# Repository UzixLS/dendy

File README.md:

## Dendy
Yet another Dendy (Famicom) clone - 8-bit home video game console

[(more random photos there)](https://cloud.err200.net/index.php/s/73TR85tYZkMm8Ax?path=%2Fdendy)

- PCB optimized for NewGame's case
- Almost all components is DIP (THT)
- 9-12V DC power supply with any polarity
- Step-down switching regulator
- PNP+NPN transistors-based video amplifier
- OpAmp-based audio mixer/amplifier
- Two switchable quartz crystals (PAL+NTSC)

### Changelog & current status
* Rev.A - first release. Please note the [errata](pcb/rev.A/ERRATA.txt)
* Rev.B:
    - Reworked crystal generator circuit
    - Tuned pcb's dimensions and holes placement for better compatibility with enclosures
    - Various minor changes and improvements
* Rev.B1:
    - Power switch moved up to 0.5mm
    - Various minor changes and improvements

### Credits
I want to express my appreciation to the
 - megawalkman
 - HardWareMan
 - lm2000
 - HotPixel

authors of the following projects, which served as inspiration and as reference for my development:

- https://www.emu-land.net/forum/index.php/topic,75737.0.html - Dendy Classic/Junior Steepler Remake
- https://www.emu-land.net/forum/index.php/topic,78815.0.html - Dendy Junior Remastered
- https://github.com/mleonid2000/dendy_junior_remastered - Dendy Junior Remastered
- https://github.com/HotPixelChannel/Candy_8bit - Candy 8bit system

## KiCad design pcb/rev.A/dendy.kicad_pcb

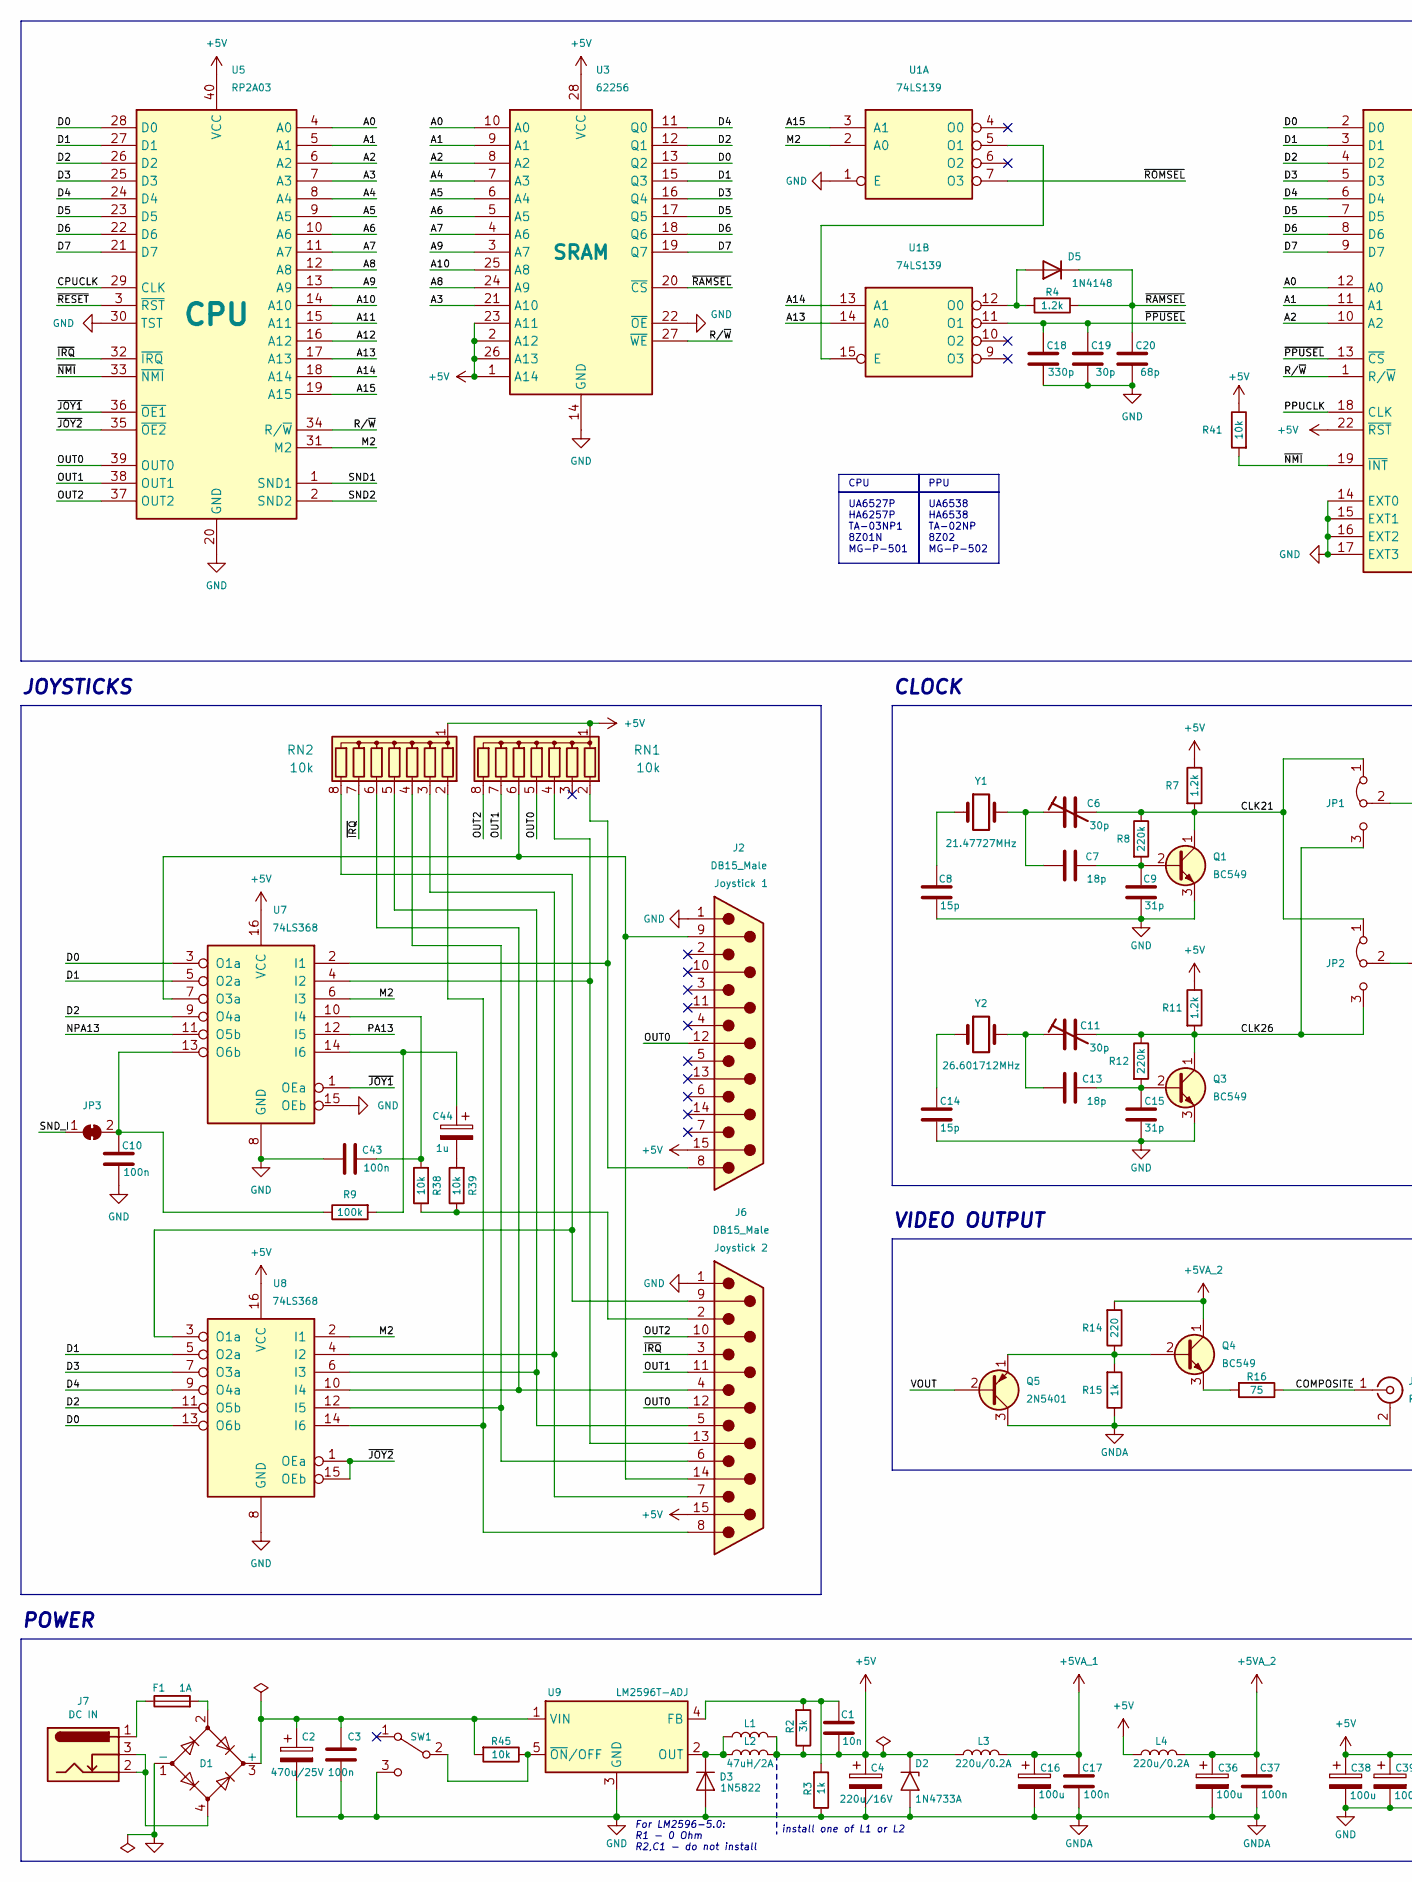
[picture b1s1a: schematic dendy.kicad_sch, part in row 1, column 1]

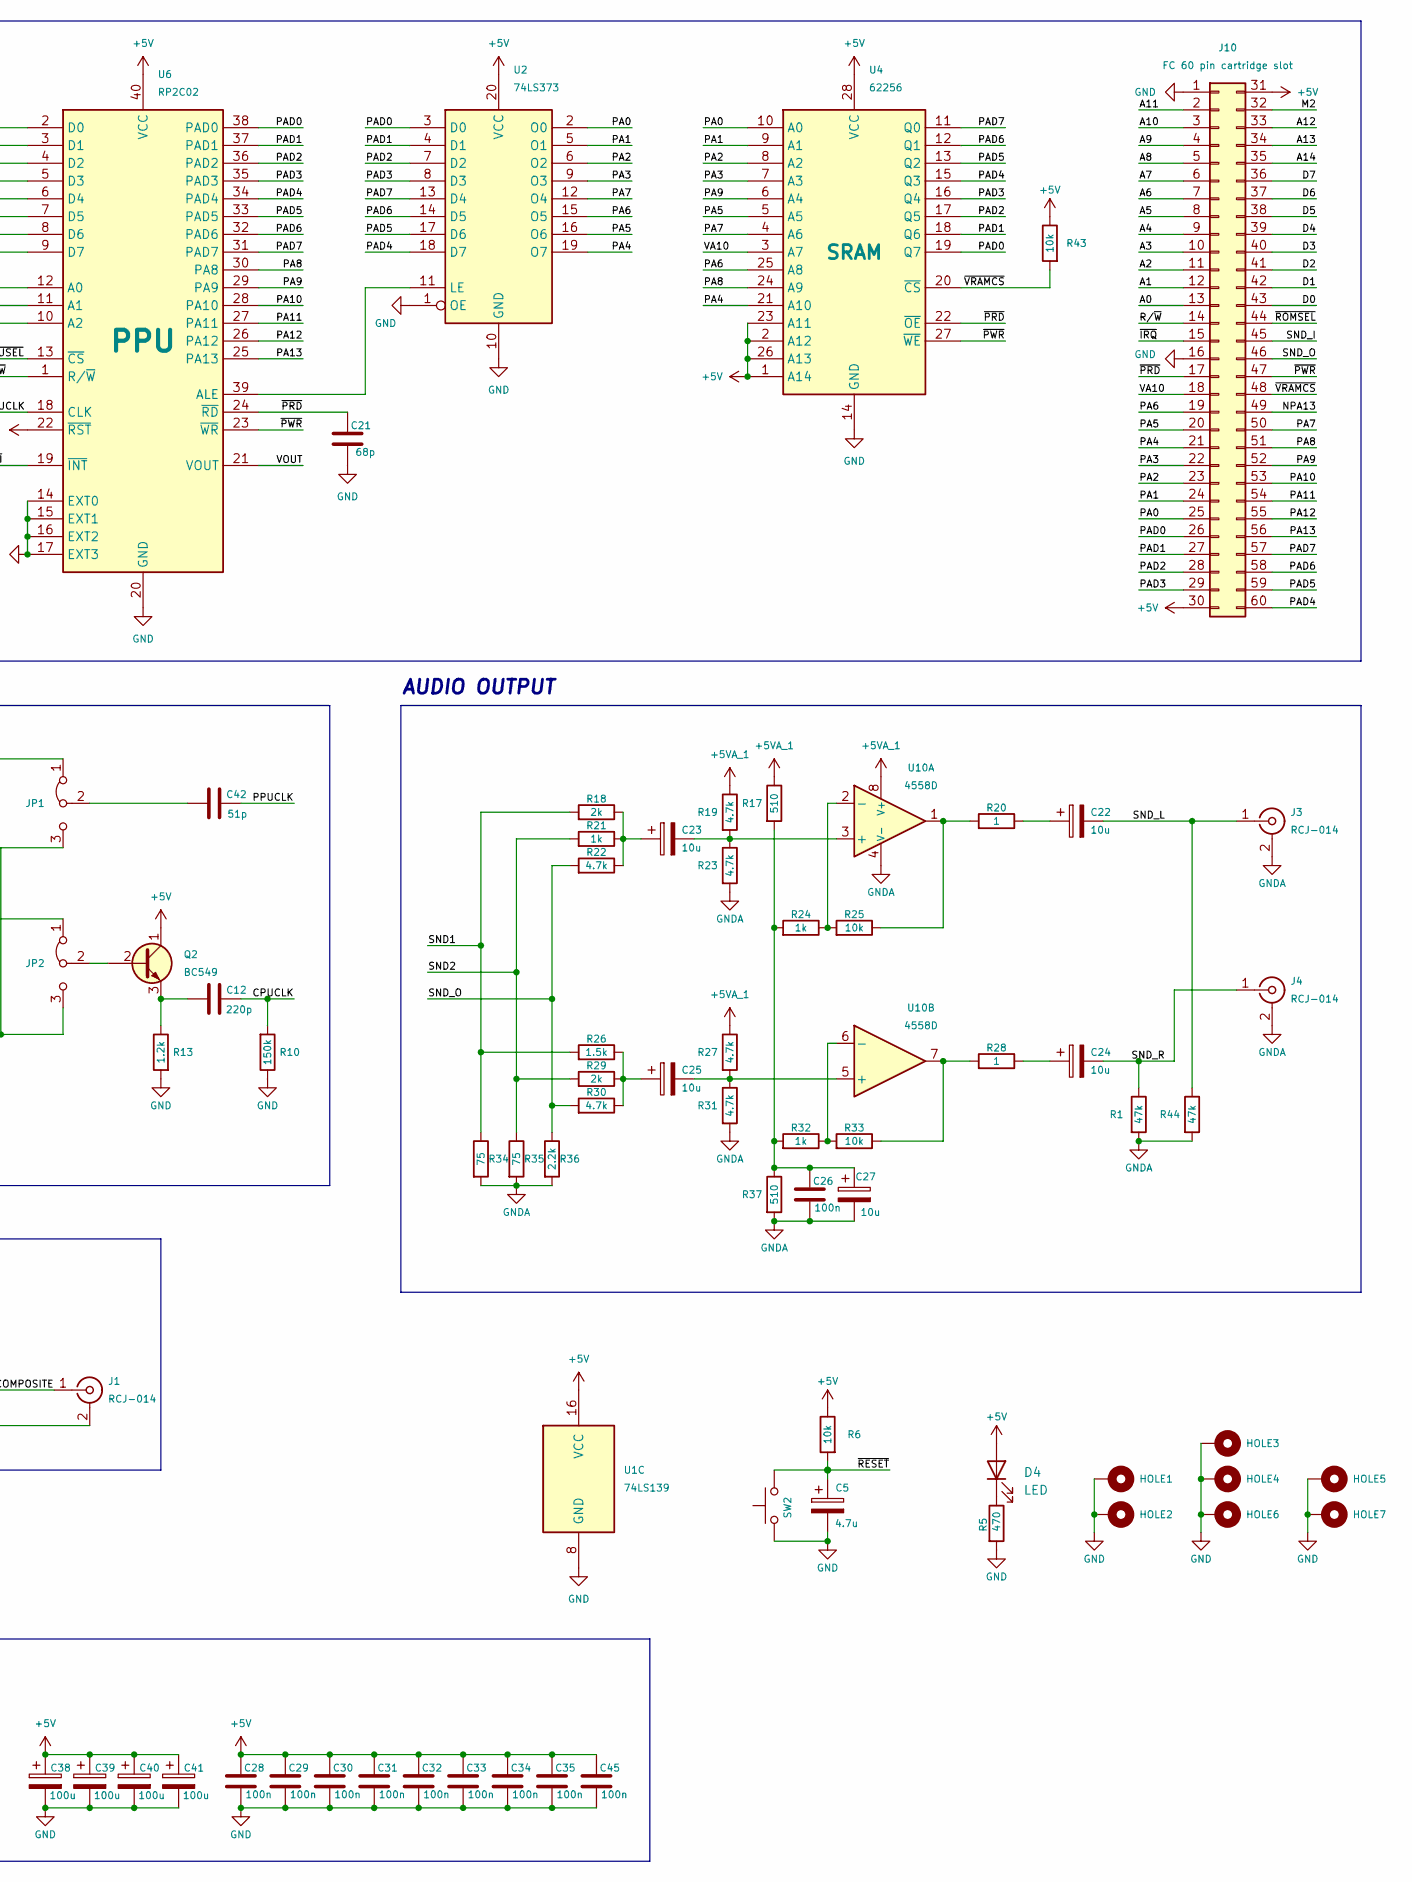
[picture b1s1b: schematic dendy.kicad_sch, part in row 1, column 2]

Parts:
C1: 10n; C_Disc_D5.0mm_W2.5mm_P2.50mm
C2: 470u/25V; CP_Radial_D10.0mm_P5.00mm
C3, C10, C17, C26, C28, C29, C30, C31, C32, C33, C34, C35, C37, C43, C45: 100n; C_Disc_D5.0mm_W2.5mm_P2.50mm
C4: 220u/16V; CP_Radial_D8.0mm_P3.50mm
C5: 4.7u; CP_Radial_D4.0mm_P2.00mm
C6, C11: 30p; C_Trimmer_GKU_L5.6mm_W5.0mm_P5.8mm
C7, C13: 18p; C_Disc_D5.0mm_W2.5mm_P2.50mm
C8, C14: 15p; C_Disc_D5.0mm_W2.5mm_P2.50mm
C9, C15: 31p; C_Disc_D5.0mm_W2.5mm_P2.50mm
C12: 220p; C_Disc_D5.0mm_W2.5mm_P2.50mm
C16, C36, C38, C39, C40, C41: 100u; CP_Radial_D6.3mm_P2.50mm
C18: 330p; C_Disc_D5.0mm_W2.5mm_P2.50mm
C19: 30p; C_Disc_D5.0mm_W2.5mm_P2.50mm
C20, C21: 68p; C_Disc_D5.0mm_W2.5mm_P2.50mm
C22, C23, C24, C25, C27: 10u; CP_Radial_D4.0mm_P2.00mm
C42: 51p; C_Disc_D5.0mm_W2.5mm_P2.50mm
C44: 1u; CP_Radial_D4.0mm_P2.00mm
D1: 2W10; Diode_Bridge_Round_D10.0mm
D2: 1N4733A; D_DO-41_SOD81_P10.16mm_Horizontal
D3: 1N5822; D_DO-201AD_P15.24mm_Horizontal
D4: LED; LED_D5.0mm
D5: 1N4148; D_DO-35_SOD27_P7.62mm_Horizontal
F1: 1A; Fuse_1812_4532Metric_Pad1.30x3.40mm_HandSolder
HOLE1: HOLE; MountingHole_3.2mm_M3_Pad_Via
HOLE2: HOLE; MountingHole_4mm_Pad_Via
HOLE3, HOLE4, HOLE5, HOLE6, HOLE7: HOLE; MountingHole_3.2mm_M3_DIN965_Pad
J1, J3, J4: RCJ-014; CUI_RCJ-01X
J2, J6: DB15_Male; DSUB-15_Male_Horizontal_P2.77x2.54mm_EdgePinOffset9.40mm
J7: DS-210; BarrelJack_Horizontal
J10: FC 60 pin cartridge slot; FC60
JP1, JP2: Jumper_3_Bridged12; PinHeader_1x03_P2.54mm_Vertical
JP3: SolderJumper_2_Bridged; SolderJumper-2_P1.3mm_Bridged_RoundedPad1.0x1.5mm
L1: 47uH/2A; L_12x12mm_H8mm
L2: 47uH/2A; L_Radial_D8.7mm_P5.00mm_Fastron_07HCP
L3, L4: 220u/0.2A; L_Radial_D8.7mm_P5.00mm_Fastron_07HCP
Q1, Q2, Q3, Q4: BC549; TO-92_Inline_Wide_CBE
Q5: 2N5401; TO-92_Inline_Wide_EBC
R1, R44: 47k; R_Axial_DIN0207_L6.3mm_D2.5mm_P7.62mm_Horizontal
R2: 3k; R_Axial_DIN0207_L6.3mm_D2.5mm_P7.62mm_Horizontal
R3, R15, R21, R24, R32: 1k; R_Axial_DIN0207_L6.3mm_D2.5mm_P7.62mm_Horizontal
R4, R7, R11, R13: 1.2k; R_Axial_DIN0207_L6.3mm_D2.5mm_P7.62mm_Horizontal
R5: 470; R_Axial_DIN0207_L6.3mm_D2.5mm_P7.62mm_Horizontal
R6, R25, R33, R38, R39, R41, R43, R45: 10k; R_Axial_DIN0207_L6.3mm_D2.5mm_P7.62mm_Horizontal
R8, R12: 220k; R_Axial_DIN0207_L6.3mm_D2.5mm_P7.62mm_Horizontal
R9: 100k; R_Axial_DIN0207_L6.3mm_D2.5mm_P7.62mm_Horizontal
R10: 150k; R_Axial_DIN0207_L6.3mm_D2.5mm_P7.62mm_Horizontal
R14: 220; R_Axial_DIN0207_L6.3mm_D2.5mm_P7.62mm_Horizontal
R16, R34, R35: 75; R_Axial_DIN0207_L6.3mm_D2.5mm_P7.62mm_Horizontal
R17, R37: 510; R_Axial_DIN0207_L6.3mm_D2.5mm_P7.62mm_Horizontal
R18, R29: 2k; R_Axial_DIN0207_L6.3mm_D2.5mm_P7.62mm_Horizontal
R19, R22, R23, R27, R30, R31: 4.7k; R_Axial_DIN0207_L6.3mm_D2.5mm_P7.62mm_Horizontal
R20, R28: 1; R_Axial_DIN0207_L6.3mm_D2.5mm_P7.62mm_Horizontal
R26: 1.5k; R_Axial_DIN0207_L6.3mm_D2.5mm_P7.62mm_Horizontal
R36: 2.2k; R_Axial_DIN0207_L6.3mm_D2.5mm_P7.62mm_Horizontal
RN1, RN2: 10k; R_Array_SIP8
SW1: SW_SPDT; SS12F44G5
SW2: Button THT; FC_Reset_Switch_Universal
U1: 74LS139; DIP-16_W7.62mm
U2: 74LS373; DIP-20_W7.62mm
U3, U4: 62256; DIP-28_W7.62mm
U5: RP2A03; DIP-40_W15.24mm_Socket
U6: RP2C02; DIP-40_W15.24mm_Socket
U7, U8: 74LS368; DIP-16_W7.62mm
U9: LM2596T-ADJ; TO-220-263-5_Horizontal_TabDown
U10: 4558D; DIP-8_W7.62mm_LongPads
Y1: 21.47727MHz; Crystal_HC49-U_Vertical
Y2: 26.601712MHz; Crystal_HC49-U_Vertical

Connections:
+5V: C1.1, C4.1, C28.2, C29.2, C30.2, C31.2, C32.2, C33.2, C34.2, C35.2, C38.1, C39.1, C40.1, C41.1, C45.2, D2.1 (A1), D4.2 (A), J2.15, J6.15, J10.30, J10.31, L1.2, L2.2, L3.1, L4.1, Q2.1 (C), R2.1, R6.1, R7.1, R11.1, R41.1, R43.1, RN1.1 (common), RN2.1 (common), U1.16 (VCC), U2.20 (VCC), U3.1 (A14), U3.2 (A12), U3.23 (A11), U3.26 (A13), U3.28 (VCC), U4.1 (A14), U4.2 (A12), U4.23 (A11), U4.26 (A13), U4.28 (VCC), U5.40 (VCC), U6.22 (~RST), U6.40 (VCC), U7.16 (VCC), U8.16 (VCC)
+5VA_1: C16.1, C17.2, L3.2, R17.1, R19.1, R27.1, U10.8 (V+)
+5VA_2: C36.1, C37.2, L4.2, Q4.1 (C), R14.2
/A0: J10.13, U3.10 (A0), U5.4 (A0), U6.12 (A0)
/A1: J10.12, U3.9 (A1), U5.5 (A1), U6.11 (A1)
/A2: J10.11, U3.8 (A2), U5.6 (A2), U6.10 (A2)
/A3: J10.10, U3.21 (A10), U5.7 (A3)
/A4: J10.9, U3.7 (A3), U5.8 (A4)
/A5: J10.8, U3.6 (A4), U5.9 (A5)
/A6: J10.7, U3.5 (A5), U5.10 (A6)
/A7: J10.6, U3.4 (A6), U5.11 (A7)
/A8: J10.5, U3.24 (A9), U5.12 (A8)
/A9: J10.4, U3.3 (A7), U5.13 (A9)
/A10: J10.3, U3.25 (A8), U5.14 (A10)
/A11: J10.2, U5.15 (A11)
/A12: J10.33, U5.16 (A12)
/A13: J10.34, U1.14 (A0), U5.17 (A13)
/A14: J10.35, U1.13 (A1), U5.18 (A14)
/A15: U1.3 (A1), U5.19 (A15)
/CLK21: C6.2, JP1.1 (A), JP2.1 (A), Q1.1 (C), R7.2, R8.1
/CLK26: C11.2, JP1.3 (B), JP2.3 (B), Q3.1 (C), R11.2, R12.1
/COMPOSITE: J1.1 (In), R16.1
/CPUCLK: C12.2, R10.2, U5.29 (CLK)
/D0: J10.43, U3.13 (Q2), U5.28 (D0), U6.2 (D0), U7.3 (O1a), U8.13 (O6b)
/D1: J10.42, U3.15 (Q3), U5.27 (D1), U6.3 (D1), U7.5 (O2a), U8.5 (O2a)
/D2: J10.41, U3.12 (Q1), U5.26 (D2), U6.4 (D2), U7.9 (O4a), U8.11 (O5b)
/D3: J10.40, U3.16 (Q4), U5.25 (D3), U6.5 (D3), U8.7 (O3a)
/D4: J10.39, U3.11 (Q0), U5.24 (D4), U6.6 (D4), U8.9 (O4a)
/D5: J10.38, U3.17 (Q5), U5.23 (D5), U6.7 (D5)
/D6: J10.37, U3.18 (Q6), U5.22 (D6), U6.8 (D6)
/D7: J10.36, U3.19 (Q7), U5.21 (D7), U6.9 (D7)
/M2: J10.32, U1.2 (A0), U5.31 (M2), U7.6 (I3), U8.2 (I1)
/NPA13: J10.49, U7.11 (O5b)
/OUT0: J2.12, J6.12, RN1.5 (R4), U5.39 (OUT0)
/OUT1: J6.11 (P111), RN1.7 (R6), U5.38 (OUT1)
/OUT2: J6.10, RN1.8 (R7), U5.37 (OUT2)
/PA0: J10.25, U2.2 (O0), U4.10 (A0)
/PA1: J10.24, U2.5 (O1), U4.9 (A1)
/PA2: J10.23, U2.6 (O2), U4.8 (A2)
/PA3: J10.22, U2.9 (O3), U4.7 (A3)
/PA4: J10.21, U2.19 (O7), U4.21 (A10)
/PA5: J10.20, U2.16 (O6), U4.5 (A5)
/PA6: J10.19, U2.15 (O5), U4.25 (A8)
/PA7: J10.50, U2.12 (O4), U4.4 (A6)
/PA8: J10.51, U4.24 (A9), U6.30 (PA8)
/PA9: J10.52, U4.6 (A4), U6.29 (PA9)
/PA10: J10.53, U6.28 (PA10)
/PA11: J10.54, U6.27 (PA11)
/PA12: J10.55, U6.26 (PA12)
/PA13: J10.56, U6.25 (PA13), U7.12 (I5)
/PAD0: J10.26, U2.3 (D0), U4.19 (Q7), U6.38 (PAD0)
/PAD1: J10.27, U2.4 (D1), U4.18 (Q6), U6.37 (PAD1)
/PAD2: J10.28, U2.7 (D2), U4.17 (Q5), U6.36 (PAD2)
/PAD3: J10.29, U2.8 (D3), U4.16 (Q4), U6.35 (PAD3)
/PAD4: J10.60, U2.18 (D7), U4.15 (Q3), U6.34 (PAD4)
/PAD5: J10.59, U2.17 (D6), U4.13 (Q2), U6.33 (PAD5)
/PAD6: J10.58, U2.14 (D5), U4.12 (Q1), U6.32 (PAD6)
/PAD7: J10.57, U2.13 (D4), U4.11 (Q0), U6.31 (PAD7)
/PPUCLK: C42.2, U6.18 (CLK)
/R/~W: J10.14, U3.27 (~WE), U5.34 (R/~W), U6.1 (R/~W)
/SND1: R18.2, R26.2, R34.1, U5.1 (SND1)
/SND2: R21.2, R29.2, R35.1, U5.2 (SND2)
/SND_I: J10.45, JP3.1 (A)
/SND_L: C22.2, J3.1 (In), R44.1
/SND_O: J10.46, R22.2, R30.2, R36.1
/SND_R: C24.2, J4.1 (In), R1.1
/VA10: J10.18, U4.3 (A7)
/VOUT: Q5.2 (B), U6.21 (VOUT)
/~IRQ: J6.3, J10.15, RN2.7 (R6), U5.32 (~IRQ)
/~JOY1: U5.36 (~OE1), U7.1 (OEa)
/~JOY2: U5.35 (~OE2), U8.1 (OEa), U8.15 (OEb)
/~NMI: R41.2, U5.33 (~NMI), U6.19 (~INT)
/~PPUSEL: C18.2, C19.2, U1.11 (O1), U6.13 (~CS)
/~PRD: C21.2, J10.17, U4.22 (~OE), U6.24 (~RD)
/~PWR: J10.47, U4.27 (~WE), U6.23 (~WR)
/~RAMSEL: C20.2, D5.1 (K), R4.1, U3.20 (~CS)
/~RESET: C5.1, R6.2, SW2.2, U5.3 (~RST)
/~ROMSEL: J10.44, U1.7 (O3)
/~VRAMCS: J10.48, R43.2, U4.20 (~CS)
GND: C2.2, C3.2, C4.2, C5.2, C8.1, C9.1, C10.1, C14.1, C15.1, C16.2, C17.1, C18.1, C19.1, C20.1, C21.1, C26.1, C27.2, C28.1, C29.1, C30.1, C31.1, C32.1, C33.1, C34.1, C35.1, C36.2, C37.1, C38.2, C39.2, C40.2, C41.2, C43.1, C45.1, D1.1 (-), D2.2 (A2), D3.2 (A), HOLE1.1, HOLE2.1, HOLE3.1, HOLE4.1, HOLE5.1, HOLE6.1, HOLE7.1, J1.2 (Ext), J2.1, J3.2 (Ext), J4.2 (Ext), J6.1, J10.1, J10.16, Q1.3 (E), Q3.3 (E), Q5.3 (C), R1.2, R3.1, R5.2, R10.1, R13.2, R15.1, R23.2, R31.2, R34.2, R35.2, R36.2, R37.2, R44.2, SW1.3 (C), SW2.1, U1.1 (E), U1.8 (GND), U2.1 (OE), U2.10 (GND), U3.14 (GND), U3.22 (~OE), U4.14 (GND), U5.20 (GND), U5.30 (TST), U6.14 (EXT0), U6.15 (EXT1), U6.16 (EXT2), U6.17 (EXT3), U6.20 (GND), U7.8 (GND), U7.15 (OEb), U8.8 (GND), U9.3 (GND), U10.4 (V-)
unnamed: C6.1, C7.1, Y1.2
unnamed: C8.2, Y1.1
unnamed: C11.1, C13.1, Y2.2
unnamed: C14.2, Y2.1
unnamed: C22.1, R20.1
unnamed: C23.1, R18.1, R21.1, R22.1
unnamed: C24.1, R28.1
unnamed: C25.1, R26.1, R29.1, R30.1
unnamed: C26.2, C27.1, R17.2, R24.2, R32.2, R37.1
unnamed: C44.2, R39.2
unnamed: C2.1, C3.1, D1.3 (+), R45.2, U9.1 (VIN)
unnamed: D1.2, F1.2
unnamed: D1.4, J7.2, J7.3
unnamed: D3.1 (K), L1.1, L2.1, U9.2 (OUT)
unnamed: D4.1 (K), R5.1
unnamed: D5.2 (A), R4.2, U1.12 (O0)
unnamed: F1.1, J7.1
unnamed: J2.9, J6.14, RN1.6 (R5), U7.7 (O3a)
unnamed: J6.9, RN2.8 (R7), U8.3 (O1a)
unnamed: J6.13, RN1.4 (R3), U7.4 (I2)
unnamed: J6.2, R38.1, R39.1
unnamed: C42.1, JP1.2 (C)
unnamed: JP2.2 (C), Q2.2 (B)
unnamed: C10.2, JP3.2 (B), R9.1, U7.13 (O6b)
unnamed: C7.2, C9.2, Q1.2 (B), R8.2
unnamed: C12.1, Q2.3 (E), R13.1
unnamed: C13.2, C15.2, Q3.2 (B), R12.2
unnamed: Q4.2 (B), Q5.1 (E), R14.1, R15.2
unnamed: Q4.3 (E), R16.2
unnamed: R20.2, R25.1, U10.1
unnamed: R28.2, R33.1, U10.7
unnamed: J2.8, RN1.2 (R1), U7.2 (I1)
unnamed: J6.8, RN2.2 (R1), U8.14 (I6)
unnamed: J6.7, RN2.3 (R2), U8.4 (I2)
unnamed: J6.6, RN2.4 (R3), U8.12 (I5)
unnamed: J6.5, RN2.5 (R4), U8.6 (I3)
unnamed: J6.4, RN2.6 (R5), U8.10 (I4)
unnamed: R45.1, SW1.2 (B), U9.5 (~ON/OFF)
unnamed: U1.5 (O1), U1.15 (E)
unnamed: U2.11 (LE), U6.39 (ALE)
unnamed: C43.2, R38.2, U7.10 (I4)
unnamed: C44.1, R9.2, U7.14 (I6)
unnamed: C1.2, R2.2, R3.2, U9.4 (FB)
unnamed: C23.2, R19.2, R23.1, U10.3 (+)
unnamed: R24.1, R25.2, U10.2 (-)
unnamed: C25.2, R27.2, R31.1, U10.5 (+)
unnamed: R32.1, R33.2, U10.6 (-)

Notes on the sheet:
CPU
CLOCK
install one of L1 or L2
PPU
UA6527P HA6257P TA-03NP1 8Z01N MG-P-501
UA6538 HA6538 TA-02NP 8Z02 MG-P-502
VIDEO OUTPUT
POWER
For LM2596-5.0: R1 - 0 Ohm R2,C1 - do not install
AUDIO OUTPUT
JOYSTICKS

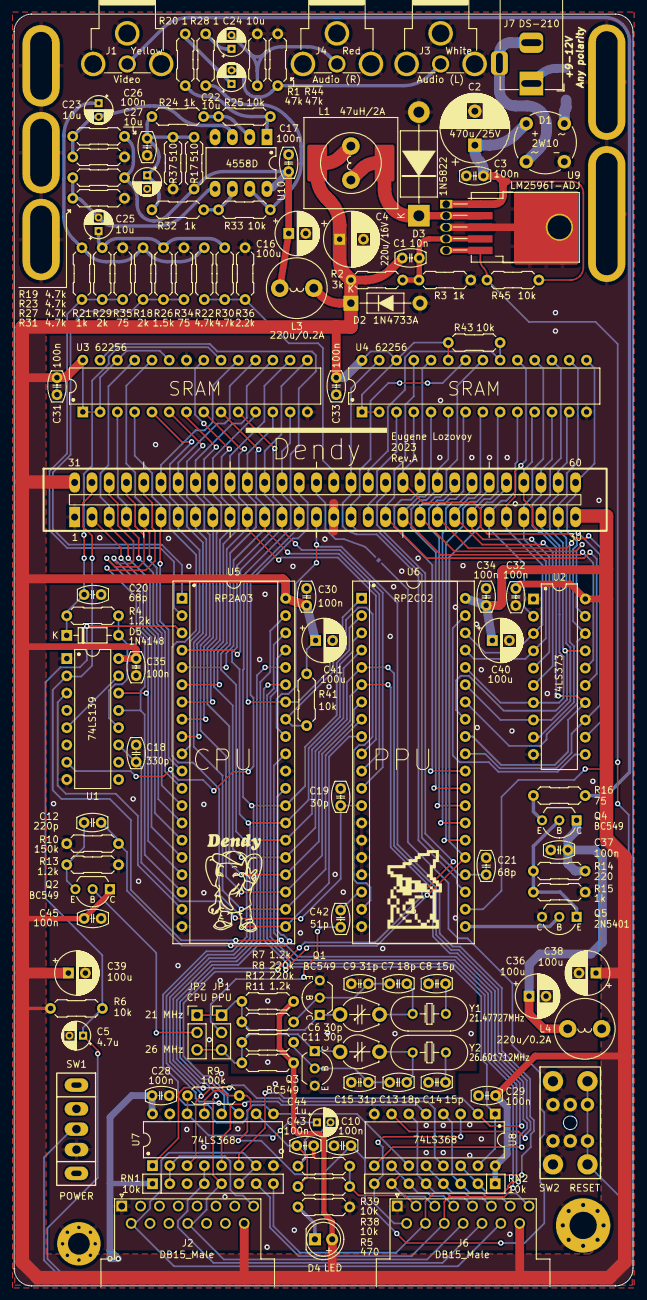
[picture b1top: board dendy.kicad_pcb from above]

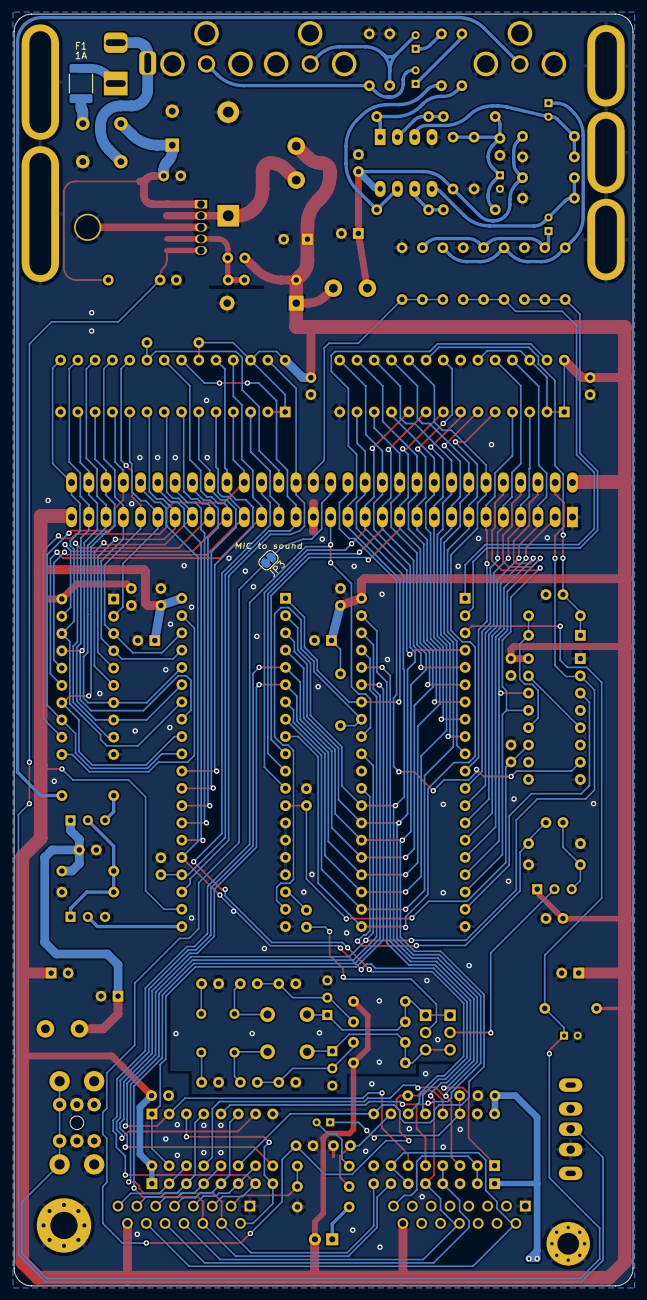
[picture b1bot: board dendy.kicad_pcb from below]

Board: 2 copper layers, 91.0 x 187.0 mm, 136 parts (2 on the bottom side), 127 nets.

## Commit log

2022-10-12 init
2022-10-12 wip pcb rev.A
2024-06-01 pcb rev.A final version
2024-06-01 add readme
2025-07-13 add pcb rev.A1
2025-07-13 add pcb rev.A errata
2025-07-13 add pcb rev.B
2025-07-15 add pcb rev.B1
